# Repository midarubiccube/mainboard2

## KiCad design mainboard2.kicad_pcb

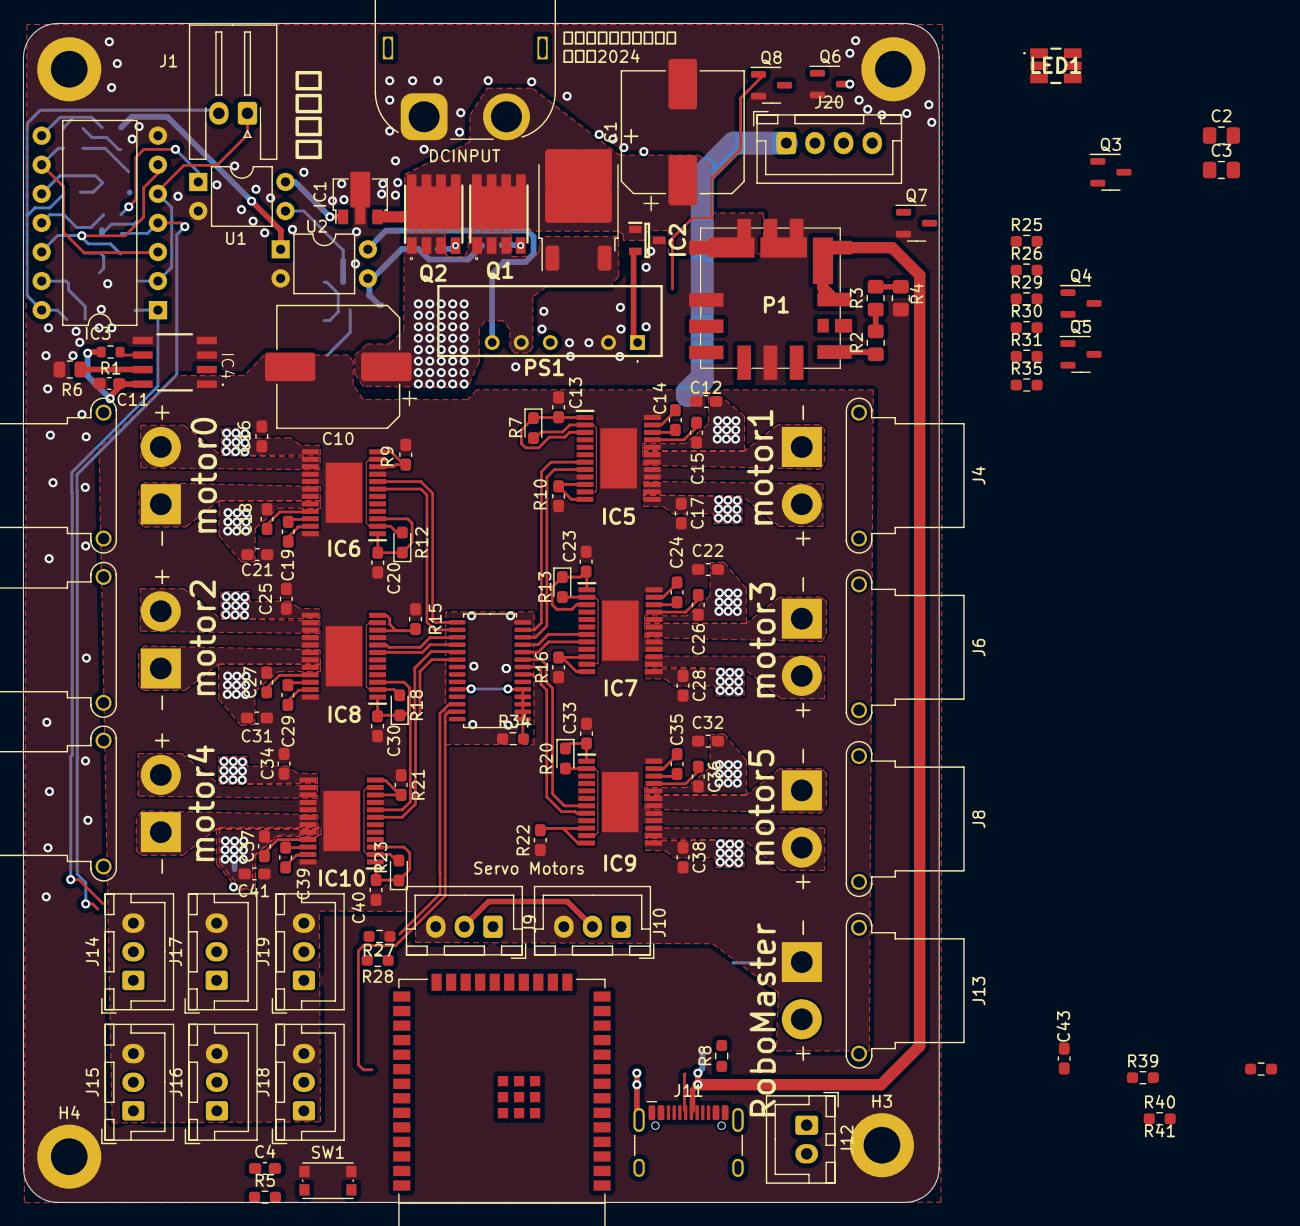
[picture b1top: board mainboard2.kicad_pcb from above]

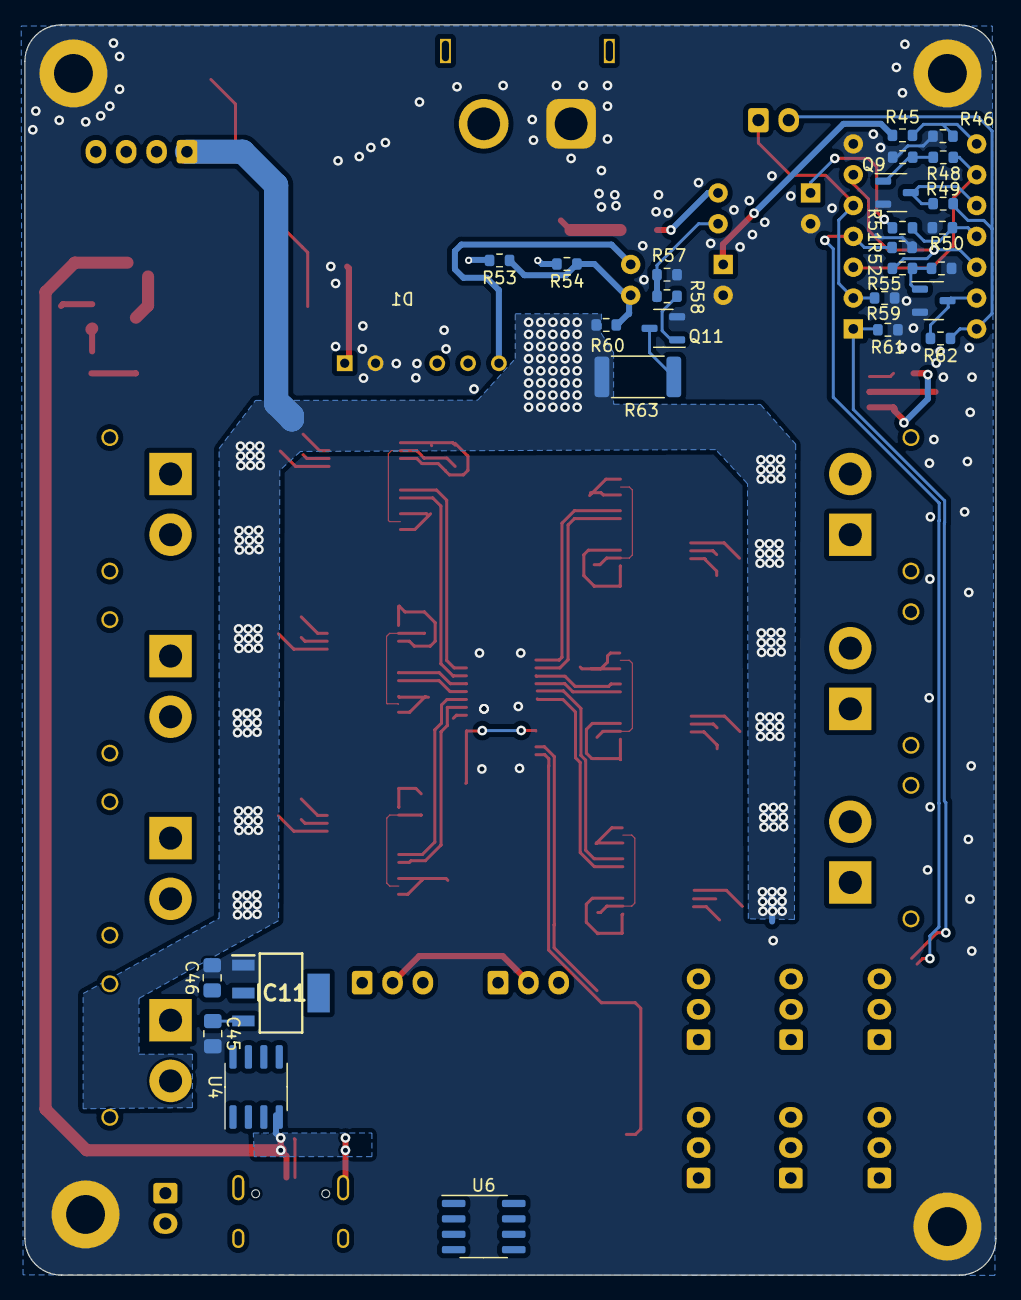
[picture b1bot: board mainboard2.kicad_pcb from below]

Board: 2 copper layers, 80.0 x 103.0 mm, 146 parts (27 on the bottom side), 129 nets.

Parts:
C1, C10: C; CP_Elec_10x10.5
C2: 22μF; C_0805_2012Metric_Pad1.18x1.45mm_HandSolder
C3: 10μF; C_0805_2012Metric_Pad1.18x1.45mm_HandSolder
C4: 0.1u; C_0603_1608Metric_Pad1.08x0.95mm_HandSolder
C11, C12, C16, C17, C21, C22, C25, C28, C31, C32, C34, C38, C41, C43: 0.1μF; C_0603_1608Metric_Pad1.08x0.95mm_HandSolder
C13, C15, C18, C20, C23, C26, C27, C30, C33, C36, C37, C40: 1μF; C_0603_1608Metric_Pad1.08x0.95mm_HandSolder
C14, C19, C24, C29, C35, C39: 47nF; C_0603_1608Metric_Pad1.08x0.95mm_HandSolder
C45, C46: 10µF; C_0805_2012Metric_Pad1.18x1.45mm_HandSolder
D1: SBR15U100CTL-13; TO-252-2
H1, H2, H3, H4: MountingHole_Pad; MountingHole_3.2mm_M3_DIN965_Pad
IC1: NJM78L12SU3-TE1; SOT-89-3
IC2: AP7375-50SA-7; SOT96P240X110-3N
IC3: TC74HC08APF; DIP-14_W10.16mm
IC4: ACS711ELCTR-25AB-T
IC5, IC6, IC7, IC8, IC9, IC10: DRV8873HPWPRQ1; SOP65P640X120-25N
IC11: AZ1117CH-3.3TRG1; SOT230P700X180-4N
J1: Conn_01x02_Socket; JST_XH_S2B-XH-A-1_1x02_P2.50mm_Horizontal
J2: Conn_01x02_Socket; AMASS_XT60PW-M_1x02_P7.20mm_Horizontal
J3, J4, J5, J6, J7, J8, J13: Conn_01x02_Socket; AMASS_XT30PW-F_1x02_P2.50mm_Horizontal
J9, J10, J14, J15, J16, J17, J18, J19: Conn_01x03_Socket; JST_XH_B3B-XH-A_1x03_P2.50mm_Vertical
J11: USB_C_Receptacle_USB2.0; USB_C_Receptacle_HCTL_HC-TYPE-C-16P-01A
J12: Conn_01x02_Socket; JST_XH_B2B-XH-A_1x02_P2.50mm_Vertical
J20: Conn_01x04_Socket; JST_XH_B4B-XH-A_1x04_P2.50mm_Vertical
LED1: NSSM065T
P1: OKLT6W12NC
PS1: MAU108; MAU118
Q1, Q2: TPH4R10ANL; SOP_ADVANCE
Q3, Q4, Q5, Q6, Q7, Q8, Q9, Q10, Q11: IRFML8244TRPBF; SOT-23-3
R1: 1kΩ; R_0603_1608Metric
R2: 1kΩ; R_0805_2012Metric_Pad1.20x1.40mm_HandSolder
R3: 330Ω; R_0805_2012Metric_Pad1.20x1.40mm_HandSolder
R4: 10Ω; R_0805_2012Metric_Pad1.20x1.40mm_HandSolder
R5, R34: 10kΩ; R_0603_1608Metric_Pad0.98x0.95mm_HandSolder
R6: 20kΩ; R_0805_2012Metric
R7, R12, R13, R18, R20, R23: 10KΩ; D_0603_1608Metric_Pad1.05x0.95mm_HandSolder
R8: 5.1k; R_0603_1608Metric_Pad0.98x0.95mm_HandSolder
R9, R10, R15, R16, R21, R22: 1.5KΩ; C_0603_1608Metric_Pad1.08x0.95mm_HandSolder
R25, R26, R27, R28, R29, R30, R31, R35, R39, R40, R41: R; R_0603_1608Metric_Pad0.98x0.95mm_HandSolder
R45, R51: 200Ω; R_0603_1608Metric
R46, R47, R49, R50, R52, R56, R59, R61, R62: 10kΩ; R_0603_1608Metric
R48, R53, R54, R55, R58: 10Ω; R_0603_1608Metric
R57, R60: 330Ω; R_0603_1608Metric
R63: 510Ω 1W; R_2512_6332Metric
SW1: SW_Push_Dual_x2; SW_Push_1P1T_NO_CK_KMR2
U1, U2: TLP785; DIP-4_W7.62mm
U3: ESP32-WROOM-E; ESP32-WROOM-32E
U4: MCP2562-E-SN; SOIC-8_3.9x4.9mm_P1.27mm
U5: PCA9685PW; TSSOP-28_4.4x9.7mm_P0.65mm
U6: CH330N; SOIC-8_3.9x4.9mm_P1.27mm

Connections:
+3.3V: C11.1, C43.1, C46.1, IC4.8 (VCC), IC11.2 (OUTPUT), IC11.4 (VOUT), R1.2, R5.1, U3.2 (3V3), U4.5 (Vio), U5.28 (VDD)
+5V: C3.1, IC3.14 (VCC), J1.2, J9.2, J10.2, J11.A4 (VBUS), J11.A9 (VBUS), J11.B4 (VBUS), J11.B9 (VBUS), J14.2, J15.2, J16.2, J17.2, J18.2, J19.2, LED1.4 (A_RED), LED1.5 (A_GREEN), LED1.6 (A_BLUE), P1.4 (Vout), P1.5 (Sence), R49.2, R62.2, U4.3 (VDD)
/385_motor1/VIN: C10.1, C12.1, C15.2, C16.1, C17.1, C18.2, C21.1, C22.1, C25.1, C26.2, C27.2, C28.1, C31.1, C32.1, C34.1, C36.2, C37.2, C38.1, C41.1, D1.1 (ANODE_1), D1.3 (ANODE_2), IC5.13 (VM_1), IC5.20 (VM_2), IC6.13 (VM_1), IC6.20 (VM_2), IC7.13 (VM_1), IC7.20 (VM_2), IC8.13 (VM_1), IC8.20 (VM_2), IC9.13 (VM_1), IC9.20 (VM_2), IC10.13 (VM_1), IC10.20 (VM_2), J20.1, PS1.5 (COMMON), Q1.1 (SOURCE_1), Q1.2 (SOURCE_2), Q1.3 (SOURCE_3), Q2.1 (SOURCE_1), Q2.2 (SOURCE_2), Q2.3 (SOURCE_3), R28.1, R60.2, R63.1
/efuse/FAULT: IC4.6 (~FAULT), R1.1
B_LED: Q3.1 (G), R25.2, U3.12 (ADC2_CH7/GPIO27)
GND: C1.2, C2.2, C3.2, C11.2, C43.2, C45.2, C46.2, H1.1, H2.1, H3.1, H4.1, IC1.2 (GND_1), IC2.3 (GND), IC3.7 (GND), IC4.3 (IP-_1), IC4.4 (IP-_2), IC4.5 (GND), IC11.1 (ADJ/GND), J2.1, P1.1 (ON/OFF), P1.3 (GND), P1.7 (GND), PS1.2 (-VIN), Q3.2 (S), Q4.2 (S), Q5.2 (S), Q6.2 (S), Q7.2 (S), Q8.2 (S), Q9.2 (S), Q10.2 (S), Q11.2 (S), R4.2, R6.2, R25.1, R27.2, R30.1, R34.2, R35.1, R39.1, R40.1, R41.1, R46.2, R47.1, R50.2, R52.2, R56.1, R57.1, R59.1, R61.1, SW1.1 (C), U1.2, U2.2, U5.14 (VSS)
GND1: C10.2, C12.2, C13.2, C16.2, C17.2, C20.2, C21.2, C22.2, C23.2, C25.2, C28.2, C30.2, C31.2, C32.2, C33.2, C34.2, C38.2, C40.2, C41.2, IC4.1 (IP+_1), IC4.2 (IP+_2), IC5.9 (DISABLE), IC5.16 (SRC_1), IC5.17 (SRC_2), IC5.24 (GND_1), IC5.25 (GND_2), IC6.9 (DISABLE), IC6.16 (SRC_1), IC6.17 (SRC_2), IC6.24 (GND_1), IC6.25 (GND_2), IC7.9 (DISABLE), IC7.16 (SRC_1), IC7.17 (SRC_2), IC7.24 (GND_1), IC7.25 (GND_2), IC8.9 (DISABLE), IC8.16 (SRC_1), IC8.17 (SRC_2), IC8.24 (GND_1), IC8.25 (GND_2), IC9.9 (DISABLE), IC9.16 (SRC_1), IC9.17 (SRC_2), IC9.24 (GND_1), IC9.25 (GND_2), IC10.9 (DISABLE), IC10.16 (SRC_1), IC10.17 (SRC_2), IC10.24 (GND_1), IC10.25 (GND_2), J9.3, J10.3, J13.1, J14.3, J15.3, J16.3, J17.3, J18.3, J19.3, R9.2, R10.2, R15.2, R16.2, R21.2, R22.2
GNDA: C4.1, J11.A1 (GND), J11.A12 (GND), J11.B1 (GND), J11.B12 (GND), J11.S1 (SHIELD), R8.2, U4.2 (VSS), U4.8 (STBY), U6.3 (GND)
G_LED: Q4.1 (G), R30.2
HI: IC3.8 (3Y), R45.1, R46.1
Iout: IC4.7 (VIOUT), R6.1
LED_B: Q8.1 (G), R40.2, U5.6 (LED0)
LED_G: Q7.1 (G), R41.2
LED_R: Q6.1 (G), R39.2, U5.7 (LED1)
LO: IC3.11 (4Y), R50.1, R51.1
unnamed: IC1.1 (VOUT), U1.4
unnamed: IC2.2 (VOUT), PS1.1 (+VIN)
unnamed: C14.2, IC5.22 (CPH)
unnamed: C14.1, IC5.23 (CPL)
unnamed: C13.1, IC5.1 (DVDD), IC5.3 (MODE), R7.1
unnamed: IC5.10 (IPROPI1), IC5.12 (IPROPI2), R10.1
unnamed: IC5.2 (NFAULT), IC5.11 (NSLEEP), R7.2
unnamed: IC5.18 (OUT1_1), IC5.19 (OUT1_2), J4.1
unnamed: IC5.14 (OUT2_1), IC5.15 (OUT2_2), J4.2
unnamed: C15.1, IC5.21 (VCP)
unnamed: C19.2, IC6.22 (CPH)
unnamed: C19.1, IC6.23 (CPL)
unnamed: C20.1, IC6.1 (DVDD), IC6.3 (MODE), R12.1
unnamed: IC6.10 (IPROPI1), IC6.12 (IPROPI2), R9.1
unnamed: IC6.2 (NFAULT), IC6.11 (NSLEEP), R12.2
unnamed: IC6.18 (OUT1_1), IC6.19 (OUT1_2), J3.1
unnamed: IC6.14 (OUT2_1), IC6.15 (OUT2_2), J3.2
unnamed: C18.1, IC6.21 (VCP)
unnamed: C24.2, IC7.22 (CPH)
unnamed: C24.1, IC7.23 (CPL)
unnamed: C23.1, IC7.1 (DVDD), IC7.3 (MODE), R13.1
unnamed: IC7.10 (IPROPI1), IC7.12 (IPROPI2), R16.1
unnamed: IC7.2 (NFAULT), IC7.11 (NSLEEP), R13.2
unnamed: IC7.18 (OUT1_1), IC7.19 (OUT1_2), J6.1
unnamed: IC7.14 (OUT2_1), IC7.15 (OUT2_2), J6.2
unnamed: C26.1, IC7.21 (VCP)
unnamed: C29.2, IC8.22 (CPH)
unnamed: C29.1, IC8.23 (CPL)
unnamed: C30.1, IC8.1 (DVDD), IC8.3 (MODE), R18.1
unnamed: IC8.10 (IPROPI1), IC8.12 (IPROPI2), R15.1
unnamed: IC8.2 (NFAULT), IC8.11 (NSLEEP), R18.2
unnamed: IC8.18 (OUT1_1), IC8.19 (OUT1_2), J5.1
unnamed: IC8.14 (OUT2_1), IC8.15 (OUT2_2), J5.2
unnamed: C27.1, IC8.21 (VCP)
unnamed: C35.2, IC9.22 (CPH)
unnamed: C35.1, IC9.23 (CPL)
unnamed: C33.1, IC9.1 (DVDD), IC9.3 (MODE), R20.1
unnamed: IC9.10 (IPROPI1), IC9.12 (IPROPI2), R22.1
unnamed: IC9.2 (NFAULT), IC9.11 (NSLEEP), R20.2
unnamed: IC9.18 (OUT1_1), IC9.19 (OUT1_2), J8.1
unnamed: IC9.14 (OUT2_1), IC9.15 (OUT2_2), J8.2
unnamed: C36.1, IC9.21 (VCP)
unnamed: C39.2, IC10.22 (CPH)
unnamed: C39.1, IC10.23 (CPL)
unnamed: C40.1, IC10.1 (DVDD), IC10.3 (MODE), R23.1
unnamed: IC10.10 (IPROPI1), IC10.12 (IPROPI2), R21.1
unnamed: IC10.2 (NFAULT), IC10.11 (NSLEEP), R23.2
unnamed: IC10.18 (OUT1_1), IC10.19 (OUT1_2), J7.1
unnamed: IC10.14 (OUT2_1), IC10.15 (OUT2_2), J7.2
unnamed: C37.1, IC10.21 (VCP)
unnamed: C45.1, IC11.3 (INPUT)
unnamed: J11.B5 (CC2), R8.1
unnamed: J12.1, U4.7 (CANH)
unnamed: J12.2, U4.6 (CANL)
unnamed: J20.2, Q8.3 (D)
unnamed: J20.3, Q7.3 (D)
unnamed: J20.4, Q6.3 (D)
unnamed: LED1.1 (K_BLUE), R31.2
unnamed: LED1.2 (K_GREEN), R29.2
unnamed: LED1.3 (K_RED), R26.2
unnamed: P1.6 (Trim), R2.1
unnamed: PS1.6 (+VOUT), U2.4
unnamed: Q1.4 (GATE), R53.2
unnamed: Q2.4 (GATE), R54.2
unnamed: Q3.3 (D), R26.1
unnamed: Q4.3 (D), R29.1
unnamed: Q5.3 (D), R31.1
unnamed: Q9.1 (G), R47.2, R48.2
unnamed: Q10.1 (G), R55.2, R56.2
unnamed: Q11.3 (D), R63.2
unnamed: Q11.1 (G), R58.2
unnamed: R2.2, R3.1
unnamed: R3.2, R4.1
unnamed: R27.1, R28.2
unnamed: R45.2, U2.1
unnamed: R51.2, U1.1
unnamed: R53.1, R54.1, R60.1, U2.3
unnamed: R57.2, R58.1, U1.3
unnamed: R5.2, SW1.2 (D), U3.3 (EN/CHIP_PU)
unnamed: U3.1 (GND), U3.15 (GND), U3.38 (GND)
unnamed: R34.1, U5.1 (A0), U5.2 (A1), U5.3 (A2), U5.4 (A3), U5.5 (A4), U5.24 (A5)
unnamed: J11.A6 (D+), J11.B6 (D+), U6.1 (UD+)
unnamed: J11.A7 (D-), J11.B7 (D-), U6.2 (UD-)
Not_A: IC3.10 (3B), Q9.3 (D), R49.1
Not_b: IC3.13 (4B), Q10.3 (D), R62.1
PWM0: IC6.7 (EN/IN1), U5.16 (LED9)
PWM1: IC6.8 (PH/IN2), U5.15 (LED8)
PWM2: IC5.7 (EN/IN1), U5.13 (LED7)
PWM3: IC5.8 (PH/IN2), U5.12 (LED6)
PWM4: IC8.7 (EN/IN1), U5.18 (LED11)
PWM5: IC8.8 (PH/IN2), U5.17 (LED10)
PWM6: IC7.7 (EN/IN1), U5.11 (LED5)
PWM7: IC7.8 (PH/IN2), U5.10 (LED4)
PWM8: IC10.7 (EN/IN1), U5.20 (LED13)
PWM9: IC10.8 (PH/IN2), U5.19 (LED12)
PWM10: IC9.7 (EN/IN1), U5.9 (LED3)
PWM11: IC9.8 (PH/IN2), U5.8 (LED2)
PWM_A: IC3.1 (1A), R61.2, U5.21 (LED14)
PWM_B: IC3.4 (2A), R52.1, U5.22 (LED15)
PWM_a: IC3.3 (1Y), IC3.9 (3A), R48.1
PWM_b: IC3.6 (2Y), IC3.12 (4A), R55.1
R_LED: Q5.1 (G), R35.2, U3.10 (DAC_1/ADC2_CH8/GPIO25)
Servo1: J18.1, U3.11 (DAC_2/ADC2_CH9/GPIO26)
Servo2: J19.1, U3.24 (ADC2_CH2/GPIO2)
Servo3: J16.1, U3.26 (ADC2_CH0/GPIO4)
Servo4: J17.1, U3.29 (GPIO5)
Servo5: J14.1, U3.27 (GPIO16)
Servo6: J15.1, U3.28 (GPIO17)
Servo7: J9.1, U3.30 (GPIO18)
Servo8: J10.1, U3.36 (GPIO22)
UART_RX: U3.35 (U0TXD/GPIO1), U6.7 (RXD)
UART_TX: U3.34 (U0RXD/GPIO3), U6.6 (TXD)
VDD: C1.1, C2.1, D1.2 (CATHODE), IC1.3 (VIN), IC2.1 (VIN), J2.2, P1.2 (Vin), Q1.5 (DRAIN_1), Q1.6 (DRAIN_2), Q1.7 (DRAIN_3), Q1.8 (DRAIN_4), Q1.9 (DRAIN_5), Q2.5 (DRAIN_1), Q2.6 (DRAIN_2), Q2.7 (DRAIN_3), Q2.8 (DRAIN_4), Q2.9 (DRAIN_5)
非常停止: IC3.2 (1B), IC3.5 (2B), J1.1, R59.2

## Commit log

2024-08-05 init commit
2024-08-06 コンデンサを追加
2024-08-07 少し変更
2024-08-10 電流センサー変更
2024-09-24 ESP32バージョン
